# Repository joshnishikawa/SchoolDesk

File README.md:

# SchoolDesk
( a plug-and-play velocity-sensitive USB MIDI drum controller)
--------------------------------------------------------------------------------

*NOTE: School Desk is a controller. It is not a sound synthesizer
     * nor is there a sound bank of any kind. It only sends MIDI messages
     * to trigger sounds in a Digital Audio Workstation (DAW).
     * You must have your DAW open and have School Desk assigned to control an
     * instrument with its own soundbank or synthesis in the DAW.
     
Plug your School Desk into a USB port and it will be automatically recognized
as a MIDI controller and should appear as "School Desk" in your DAW.

School Desk has two banks which store 11 sounds each.

These are the default sounds for Bank 1:
 __________ __________ __________ __________ __________ __________
|1         |2         |3         |4         |5         |6         |
| Crash 1  |  Hi Tom  | Low Tom  | Splash   | Ride Bell| Crash 2  |
|          |          |          |          |          |          |
'----------^----------^----------^----------^----------^----------'
|7           |8           |9            |10          |11          |
| Snare Drum |  Hi-Hats   |  Floor Tom  | Ride Cymbal| Kick Drum  |
|            |            |             |            |  Note #36  |
'------------^------------^-------------^------------^------------'

These are the default sounds for Bank 2:
 __________ __________ __________ __________ __________ __________
|1         |2         |3         |4         |5         |6         |
| Crash 1  |  Hi Tom  | Low Tom  | Splash   | Ride Bell| Crash 2  |
|          |          |          |          |          |          |
'----------^----------^----------^----------^----------^----------'
|7           |8           |9            |10          |11          |
| Snare Drum |  Hi-Hats   |  Floor Tom  | Ride Cymbal| Kick Drum  |
|            |            |             |            |            |
'------------^------------^-------------^------------^------------'

You can switch between banks 1 and 2 by pressing and releasing
The "Edit" button.

--------------------------------------------------------------------------------

Different sounds can also be assigned to each pad by following these steps:

1. Press and HOLD the Edit button on the right side of the controller.
    The orange LED will light up.

2. While holding this button, tap the pad you want to edit.
    The orange LED will now begin to blink and you can release the Edit button.

3. Now the controller is in "Program Mode" and the sound for the pad you
    tapped can be changed by turning the knob on the back of the controller.
    Continue to trigger the pad until you find the desired sound.*

4. While in program mode (indicated by the blinking LED) you may change
    the sounds for any of the pads by first triggering the pad and then
    turning the knob while triggering the pad until you reach the desired sound.

5. When you have finished choosing your sounds. Press the Edit button once
    again. The sounds you selected will be saved to internal memory and will be
    available the next time you plug in School Desk (unltil you change them).
    
    *NOTE: Turning the knob will cycle though note numbers 35 through 81.
          * These are the numbers that are assigned to drum sounds
          * according to the general MIDI standard. 
          * These numbers are as follows:

          * GM DRUM SOUNDS
      MIDI# - NOTE - SOUND
        35    B  0   Acoustic Bass Drum
        36    C  1   Bass Drum 1
        37    C# 1   Side Stick
        38    D  1   Acoustic Snare
        39    D# 1   Hand Clap
        40    E  1   Electric Snare
        41    F  1   Low Floor Tom
        42    F# 1   Closed Hi Hat
        43    G  1   High Floor Tom
        44    G# 1   Pedal Hi-Hat
        45    A  1   Low Tom
        46    A# 1   Open Hi-Hat
        47    B  1   Low-Mid Tom
        48    C  2   Hi-Mid Tom
        49    C# 2   Crash Cymbal 1
        50    D  2   High Tom
        51    D# 2   Ride Cymbal 1
        52    E  2   Chinese Cymbal
        53    F  2   Ride Bell
        54    F# 2   Tambourine
        55    G  2   Splash Cymbal
        56    G# 2   Cowbell
        57    A  2   Crash Cymbal 2
        58    A# 2   Vibraslap
        59    B  2   Ride Cymbal 2
        60    C  3   Hi Bongo
        61    C# 3   Low Bongo
        62    D  3   Mute Hi Conga
        63    D# 3   Open Hi Conga
        64    E  3   Low Conga
        65    F  3   High Timbale
        66    F# 3   Low Timbale
        67    G  3   High Agogo
        68    G# 3   Low Agogo
        69    A  3   Cabasa
        70    A# 3   Maracas
        71    B  3   Short Whistle
        72    C  4   Long Whistle
        73    C# 4   Short Guiro
        74    D  4   Long Guiro
        75    D# 4   Claves
        76    E  4   Hi Wood Block
        77    F  4   Low Wood Block
        78    F# 4   Mute Cuica
        79    G  4   Open Cuica
        80    G# 4   Mute Triangle
        81    A  4   Open Triangle

    * Any note which does not have a sound assigned to it in your DAW
    * will not be audible.

--------------------------------------------------------------------------------

You may also set any (or all) of the pads to be used as expression controllers.

These are the Control Chang numbers used for Bank 1:
 __________ __________ __________ __________ __________ __________
|1         |2         |3         |4         |5         |6         |
|          |          |          |          |          |          |
|  CC #20  |  CC #21  |  CC #22  |  CC #23  |  CC #24  |  CC #25  |
'----------^----------^----------^----------^----------^----------'
|7           |8           |9            |10          |11          |
|            |            |             |            |            |
|   CC #26   |   CC #27   |   CC #28    |   CC #29  |   CC #30   |
'------------^------------^-------------^------------^------------'

These are the Control Chang numbers used for Bank 2:
 __________ __________ __________ __________ __________ __________
|1         |2         |3         |4         |5         |6         |
|          |          |          |          |          |          |
|  CC #102 |  CC #103 |  CC #104 |  CC #105 |  CC #106 |  CC #107 |
'----------^----------^----------^----------^----------^----------'
|7           |8           |9            |10          |11          |
|            |            |             |            |            |
|   CC #108  |   CC #109  |   CC #110   |   CC #111  |   CC #112  |
'------------^------------^-------------^------------^------------'

A pad can be set as an expression controller by following these steps:

1. 

*NOTE: All of these Control Change numbers are otherwise 'undefined' in the
    * general MIDI specification and should therefore be safe to use.
    * However, please be aware that these numbers cannot be changed.

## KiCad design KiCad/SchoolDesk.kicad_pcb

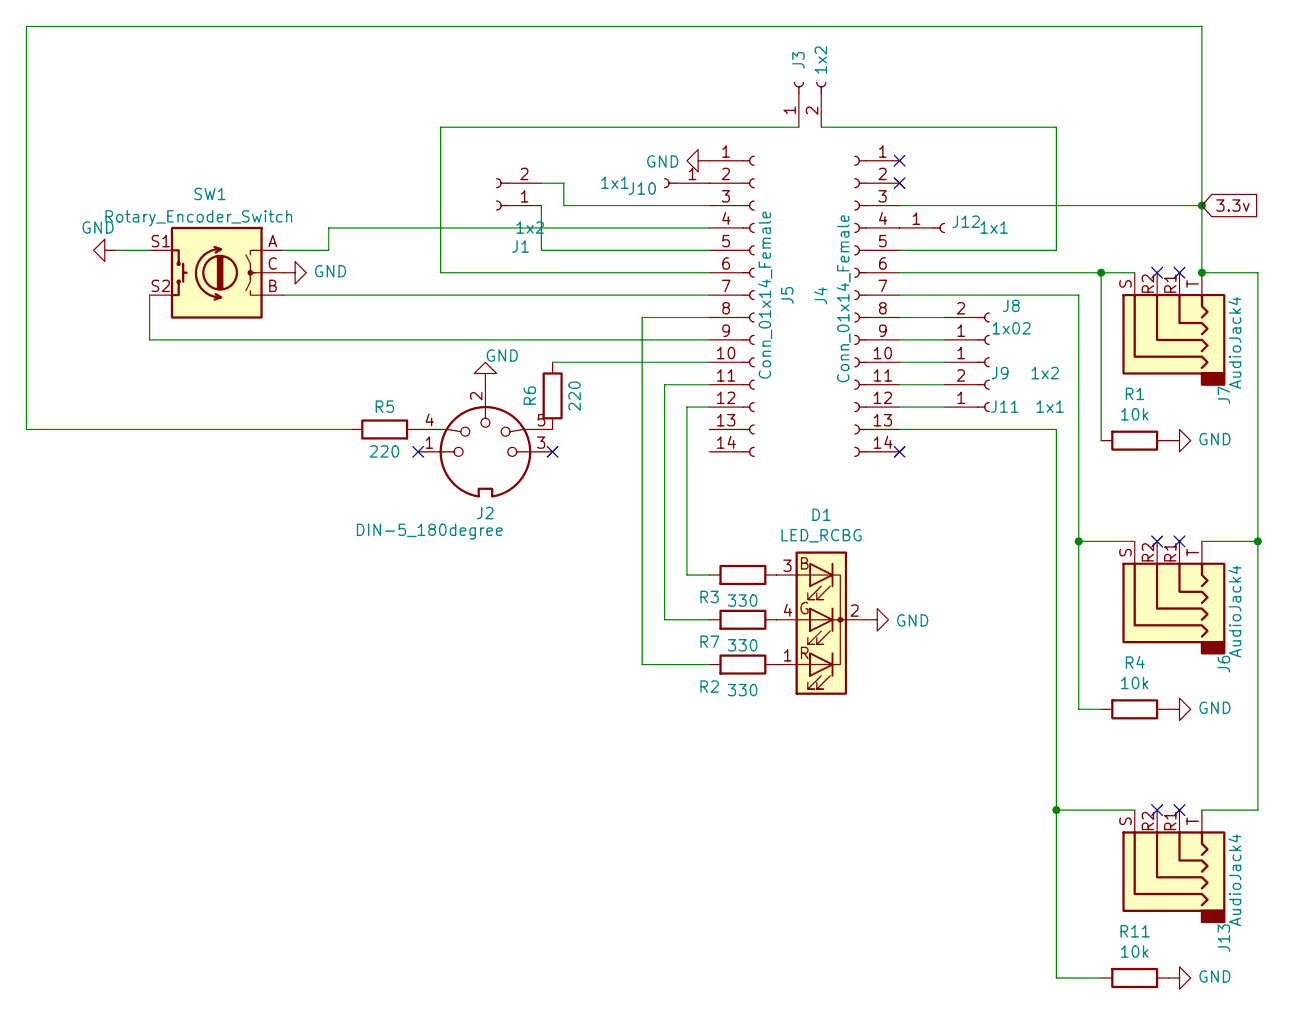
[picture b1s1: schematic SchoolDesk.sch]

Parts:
D1: LED_RCBG; LED_RGB_1210
J1, J3, J9: 1x2; Pin_Header_Straight_1x02_Pitch2.00mm
J2: DIN-5_180degree; SDS-50J
J4, J5: Conn_01x14_Female; PinSocket_1x14_P2.54mm_Vertical
J6, J7, J13: AudioJack4; Jack_3.5mm_PJ320D_Horizontal
J8: 1x02; Pin_Header_Straight_1x02_Pitch2.00mm
J10, J11, J12: 1x1; Pin_Header_Straight_1x01_Pitch2.00mm
R1, R4, R11: 10k; R_Axial_DIN0207_L6.3mm_D2.5mm_P2.54mm_Vertical
R2, R3, R7: 330; R_0805_2012Metric
R5, R6: 220; R_0805_2012Metric
SW1: Rotary_Encoder_Switch; Rotary_Encoder_Switched_PEC11R

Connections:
3.3v: J4.3, J6.T, J7.T, J13.T, R5.1
GND: D1.2 (K), J2.2, J5.1, R1.1, R4.1, R11.1, SW1.C, SW1.S1
unnamed: D1.1 (RA), R2.1
unnamed: D1.3 (BA), R3.1
unnamed: D1.4 (GA), R7.1
unnamed: J1.1, J5.5
unnamed: J1.2, J5.3
unnamed: J2.4, R5.2
unnamed: J2.5, R6.2
unnamed: J3.1, J5.6
unnamed: J3.2, J4.5
unnamed: J4.6, J7.S, R1.2
unnamed: J4.7, J6.S, R4.2
unnamed: J4.8, J8.2
unnamed: J4.9, J8.1
unnamed: J4.10, J9.1
unnamed: J4.11, J9.2
unnamed: J5.4, SW1.A
unnamed: J5.7, SW1.B
unnamed: J5.8, R2.2
unnamed: J5.9, SW1.S2
unnamed: J5.10, R6.1
unnamed: J5.11, R7.2
unnamed: J5.12, R3.2
unnamed: J5.2, J10.1
unnamed: J4.12, J11.1
unnamed: J4.4, J12.1
unnamed: J4.13, J13.S, R11.2

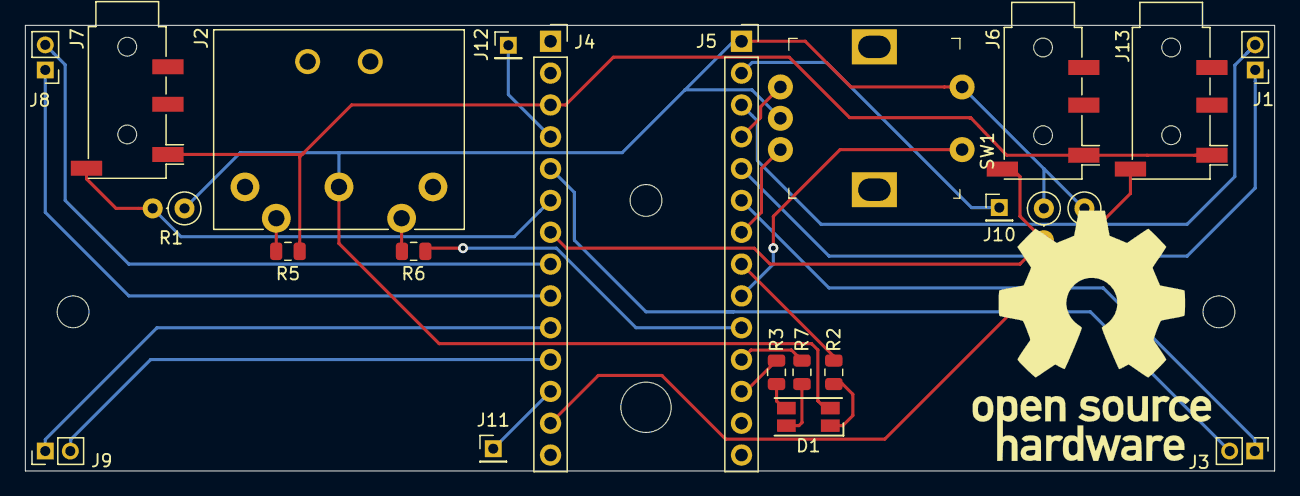
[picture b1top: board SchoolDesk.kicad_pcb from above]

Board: 2 copper layers, 99.7 x 35.6 mm, 23 parts (0 on the bottom side), 28 nets.

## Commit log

2020-01-17 Add KiCad files
2020-02-17 First (untested) commit including PCB files.
